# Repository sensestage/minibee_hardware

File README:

This repository contains the Eagle design files for the Sense/Stage MiniBee (folder minibee) and a programmer (folder programmer) for the Sense/Stage MiniBee.

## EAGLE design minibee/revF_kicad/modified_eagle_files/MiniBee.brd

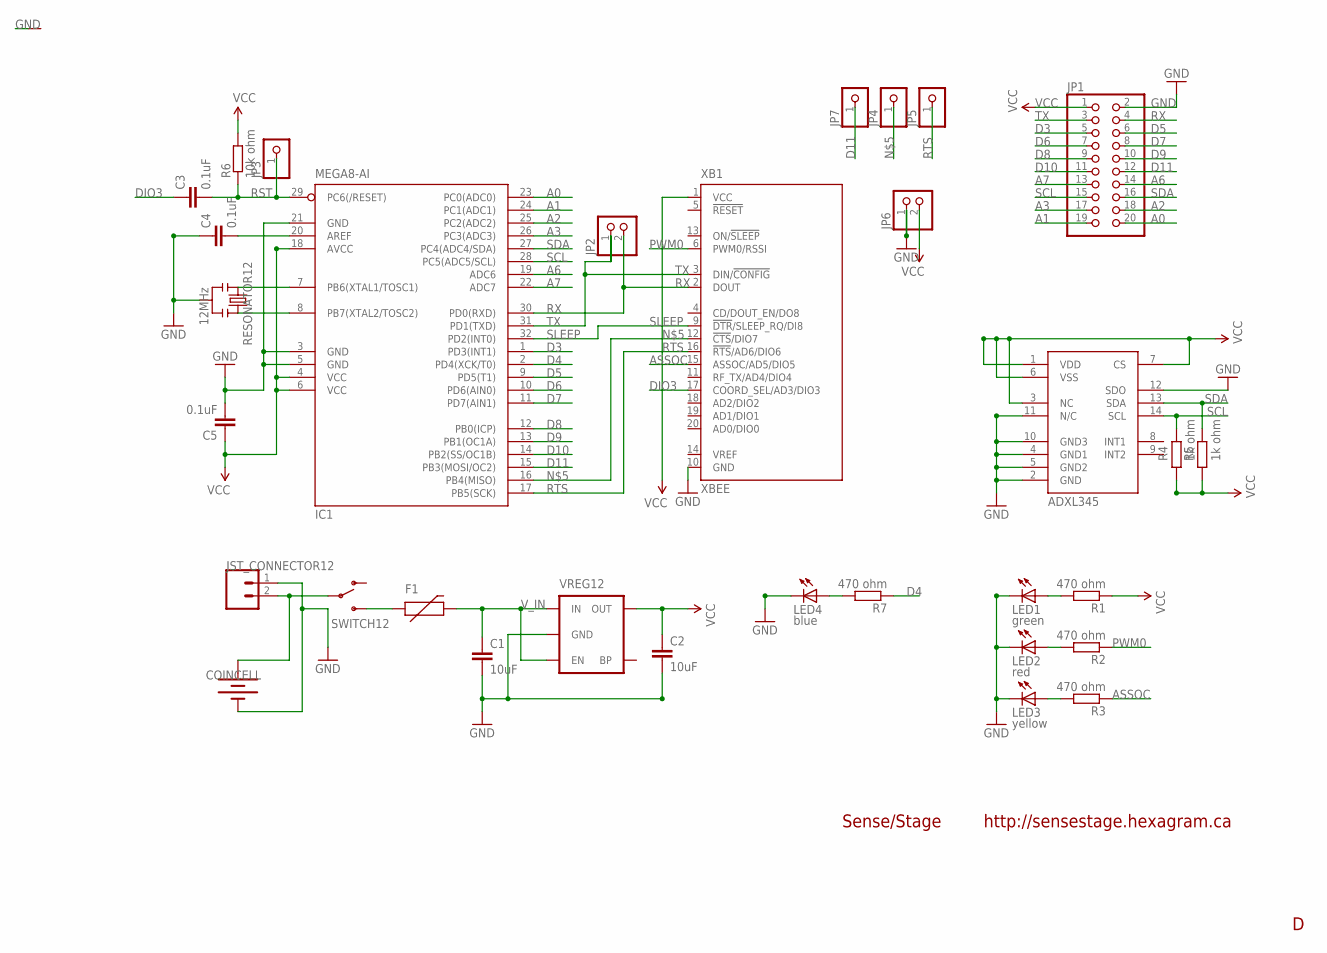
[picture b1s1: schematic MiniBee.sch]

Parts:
C1, C2: 10uF; C0805
C3, C4: 0.1uF; C0402
C5: 0.1uF; C0402K
COINCELL12: COINCELL; KEYSTONE_BATTERY_HOLDER
F1: PTCSMD; PTC-1206
IC1: MEGA8-AI; TQFP32-08
JP1: PINHD-2X10; 2X10
JP2, JP6: PINHD-1X2; 1X02
JP3, JP4, JP5, JP7: PINHD-1X1; 1X01
JST_CONNECTOR12: JST_CONNECTOR; S2B-PH
LED1: green; CHIP-LED0603
LED2: red; CHIP-LED0603
LED3: yellow; CHIP-LED0603
LED4: blue; CHIP-LED0603
R1, R2, R3, R7: 470 ohm; R0402
R4, R5: 1k ohm; R0402
R6: 10k ohm; R0402
RESONATOR12: 12MHz; RESONATOR-SMD
SWITCH12: MYSHIT_PCM_SWITCH; MYSHIT_PCM_SWITCH_RA
U1: ADXL345; LGA14
VP_0: VPDEV0; VPAC0
VREG12: V_REG_LDOSMD; SOT23-5
XB1: XBEE

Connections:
A0: IC1.23 (PC0(ADC0)), JP1.20
A1: IC1.24 (PC1(ADC1)), JP1.19
A2: IC1.25 (PC2(ADC2)), JP1.18
A3: IC1.26 (PC3(ADC3)), JP1.17
A6: IC1.19 (ADC6), JP1.14
A7: IC1.22 (ADC7), JP1.13
ASSOC: R3.1, XB1.15 (ASSOC/AD5/DIO5)
D3: IC1.1 (PD3(INT1)), JP1.5
D4: IC1.2 (PD4(XCK/T0)), R7.1
D5: IC1.9 (PD5(T1)), JP1.6
D6: IC1.10 (PD6(AIN0)), JP1.7
D7: IC1.11 (PD7(AIN1)), JP1.8
D8: IC1.12 (PB0(ICP)), JP1.9
D9: IC1.13 (PB1(OC1A)), JP1.10
D10: IC1.14 (PB2(SS/OC1B)), JP1.11
D11: IC1.15 (PB3(MOSI/OC2)), JP1.12, JP7.1
DIO3: C3.1, XB1.17 (COORD_SEL/AD3/DIO3)
GND: C1.2, C2.2, C4.1, C5.2, COINCELL12.-, IC1.3 (GND), IC1.5 (GND), IC1.21 (GND), JP1.2, JP6.1, JST_CONNECTOR12.1, LED1.C, LED2.C, LED3.C, LED4.C, RESONATOR12.2, U1.2 (GND), U1.4 (GND1), U1.5 (GND2), U1.10 (GND3), U1.11 (N/C), U1.12 (SDO), VP_0.VP, VREG12.2 (GND), XB1.10 (GND)
unnamed: IC1.7 (PB6(XTAL1/TOSC1)), RESONATOR12.1
unnamed: IC1.8 (PB7(XTAL2/TOSC2)), RESONATOR12.3
unnamed: LED1.A, R1.2
unnamed: COINCELL12.+, JST_CONNECTOR12.2, SWITCH12.2
unnamed: IC1.16 (PB4(MISO)), JP4.1, XB1.12 (!CTS!/DIO7)
unnamed: LED2.A, R2.2
unnamed: LED3.A, R3.2
unnamed: F1.1, SWITCH12.3 (S)
unnamed: C4.2, IC1.20 (AREF)
unnamed: LED4.A, R7.2
PWM0: R2.1, XB1.6 (PWM0/RSSI)
RST: C3.2, IC1.29 (PC6(/RESET)), JP3.1, R6.1
RTS: IC1.17 (PB5(SCK)), JP5.1, XB1.16 (!RTS!/AD6/DIO6)
RX: IC1.30 (PD0(RXD)), JP1.4, JP2.2, XB1.2 (DOUT)
SCL: IC1.28 (PC5(ADC5/SCL)), JP1.15, R4.2, U1.14 (SCL)
SDA: IC1.27 (PC4(ADC4/SDA)), JP1.16, R5.2, U1.13 (SDA)
SLEEP: IC1.32 (PD2(INT0)), XB1.9 (!DTR!/SLEEP_RQ/DI8)
TX: IC1.31 (PD1(TXD)), JP1.3, JP2.1, XB1.3 (DIN/!CONFIG)
VCC: C2.1, C5.1, IC1.4 (VCC), IC1.6 (VCC), IC1.18 (AVCC), JP1.1, JP6.2, R1.1, R4.1, R5.1, R6.2, U1.1 (VDD), U1.3 (NC), U1.6 (VSS), U1.7 (CS), VREG12.5 (OUT), XB1.1 (VCC)
V_IN: C1.1, F1.2, VREG12.1 (IN), VREG12.3 (EN)

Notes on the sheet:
Sense/Stage
http://sensestage.hexagram.ca

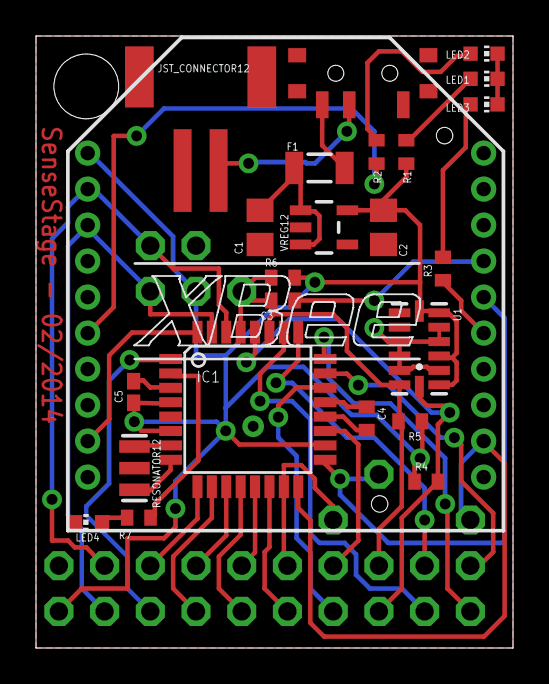
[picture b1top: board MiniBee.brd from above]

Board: 2 copper layers, 26.5 x 34.0 mm, 33 parts (1 on the bottom side), 38 nets.

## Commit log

2010-11-18 add the revision C eagle files
2010-11-18 added breakout pins for programmer for D11 and GND and Vcc (3v3)
2011-01-11 updates to the board - routing all the wires to the new pins
2011-01-11 fixed the font thickness and added some labels
2011-01-11 gerber files for the MiniBee
2011-01-17 i2c envir files, and drill file for MiniBee board.
2011-01-17 more directory cleanup actions.
2011-02-08 Start of a revision E. Uses SMD footprint headers and a different coincell holder. Also features an 8-pin programming header. Resulting in a bigger board, though routing is still tricky. Not finished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
2011-02-08 minor changes
2011-02-08 fix some routes
2011-04-07 switch around GND/3v3 and RX/TX so board is more compatible with revB.
2011-04-08 cleanup of some traces and vias; moved the ME led a bit.
2011-04-13 added one more via between ground planes.
2011-05-09 programmer board for MiniBee revD
2011-05-09 updates to the board with layers with the component orientation
2011-05-11 adjusted board to olimex specs, and added the design rules from them
2011-06-20 update to programmer board
2011-06-22 update to MiniBee board (show all layers), and fix BOM.
2011-08-26 updates to the programmer - still have to double check the new hole positions with XPlorer board
2012-08-14 reorganise directories
2012-08-20 add README file
2013-06-12 add revA for historical purposes
2013-07-04 raspberry pi xbee coordinator shield
2014-02-21 updates to the board based on feedback from manufacturer
2017-01-17 kicad conversion and fixes of revD board
2017-01-17 gerber files for modified revD
2017-01-17 updates to board: exchanged D2 and D7, other switch
2017-01-17 switch footprint, updated BOM
2017-01-17 updated gerbers for revision F
2017-01-17 update silkscreen to rev F
2017-01-18 rename BOM
2017-01-18 update board
2017-01-18 update BOM
2017-02-07 fix some traces (mostly the Vcc trace that was close to the edge)
2019-05-11 additional files for rev F
